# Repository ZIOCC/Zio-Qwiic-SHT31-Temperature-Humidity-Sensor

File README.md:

# Zio Qwiic SHT31 Temperature Humidity Sensor

> This product can be available for purchase [here](https://www.smart-prototyping.com/Zio-Qwiic-Temperature-Humidity-Sensor-SHT31).

#### Description

The SHT31 digital temperature and humidity board takes sensor technology to a new level! This board is fully calibrated and as the rest of Sensirion products, the SHT31 integrates CMOSens® technology which combines both sensors on a single silicon chip. Providing high precision data in a cost efficiency chip! 

Most of STH sensors don’t provide a true I2C interface for easy reading, but we got good news, this sensor provides multiple functions and interfaces, including I2C with two address options. Do we need to give you more reasons why we have incorporate it to our Qwiic family ecosystem :) ? In a few words this one sensor earned to be part of family for its high precision and simplicity to use.  

Let's get into some cool details! Talking about precision, it has a ±2% error on relative humidity. For the temperature measurements it is not lagging behind, with a ±0.3 °C accuracy even on extreme conditions, from -40 to 125 °C.

Just in case you would like to use this board without the Qwiic connector, we have incorporated header pins. As well as if you’d like to access the ALERT and RESET pins.

#### Specification

* Supply Voltage: 3.3V
* Accuracy
  * Relative Humidity: ±2%
  * Temperature: ±0.3 °C
* Interface: I2C (selectable address at 0x44 (default) and 0x45)
* Dimensions: 16.5 x 25.3mm
* Weight: 1.1g

#### Links

* [SHT31 Datasheet](https://www.sensirion.com/fileadmin/user_upload/customers/sensirion/Dokumente/0_Datasheets/Humidity/Sensirion_Humidity_Sensors_SHT3x_Datasheet_digital.pdf)
* [Eagle File and Schematic](https://github.com/ZIOCC/Zio-Qwiic-SHT31-Temperature-Humidity-Sensor)
* [SHT31 Library](https://github.com/adafruit/Adafruit_SHT31)

> ###### About Zio
> Zio is a new line of open sourced, compact, and grid layout boards, fully integrated for Arduino and Qwiic ecosystem. Designed ideally for wearables, robotics, small-space limitations or other on the go projects. Check out other awesome Zio products [here](https://www.smart-prototyping.com/Zio).

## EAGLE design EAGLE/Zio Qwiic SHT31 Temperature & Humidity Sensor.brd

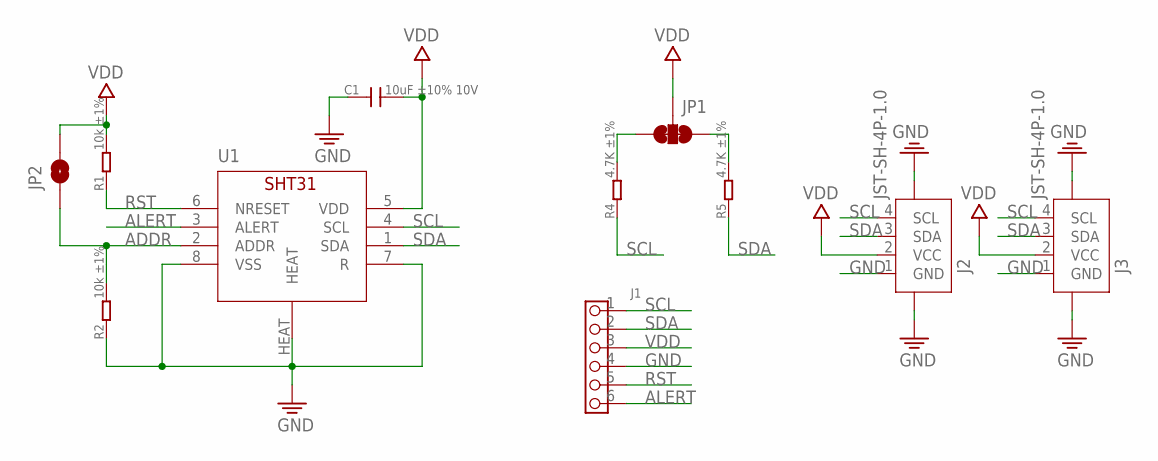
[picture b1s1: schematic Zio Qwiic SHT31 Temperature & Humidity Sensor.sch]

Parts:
C1: 10uF ±10% 10V; C0603
J1: HEADER-6P-60/35MIL; 6P-2.54-60/35MIL
J2, J3: JST-SH-4P-1.0; JST-SH-4P
JP1: SMT-JUMPER_3_2-NC_TRACE
JP2: JUMPER-SMT_2_NC_PASTE_NOCREM; SMT-JUMPER_2_NC_PASTE_SILK_NOCREM
R1, R2: 10k ±1%; R0603
R4, R5: 4.7K ±1%; R0603
U1: SHT31; DFN8

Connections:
ADDR: JP2.1, R2.2, U1.2 (ADDR)
ALERT: J1.6, U1.3 (ALERT)
GND: C1.1, J1.4, J2.1 (GND), J2.NC1 (5), J2.NC2 (6), J3.1 (GND), J3.NC1 (5), J3.NC2 (6), R2.1, U1.7 (R), U1.8 (VSS), U1.HEAT
unnamed: JP1.3, R4.2
unnamed: JP1.1, R5.2
RST: J1.5, R1.1, U1.6 (NRESET)
SCL: J1.1, J2.4 (SCL), J3.4 (SCL), R4.1, U1.4 (SCL)
SDA: J1.2, J2.3 (SDA), J3.3 (SDA), R5.1, U1.1 (SDA)
VDD: C1.2, J1.3, J2.2 (VCC), J3.2 (VCC), JP1.2, JP2.2, R1.2, U1.5 (VDD)

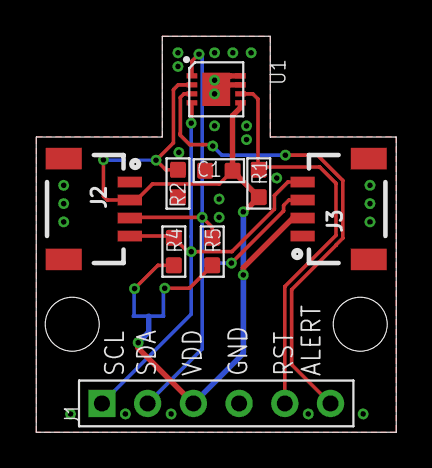
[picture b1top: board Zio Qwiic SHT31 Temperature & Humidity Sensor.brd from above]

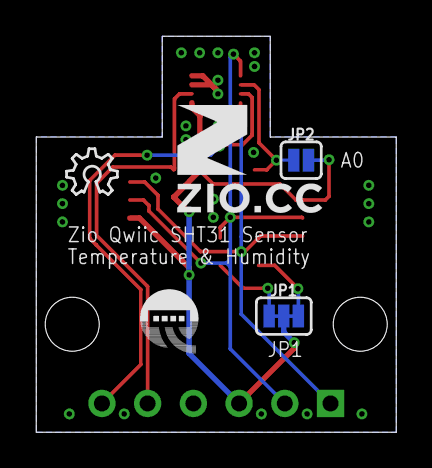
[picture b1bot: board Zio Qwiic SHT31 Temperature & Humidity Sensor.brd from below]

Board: 2 copper layers, 20.0 x 22.0 mm, 14 parts (5 on the bottom side), 9 nets.

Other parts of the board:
U$3: OSHW_6X100_NOTEXT
U$4: 6MM
U$5: QWIIC-LOGO-BASIC

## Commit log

2018-08-27 Schematic File in PDF format
